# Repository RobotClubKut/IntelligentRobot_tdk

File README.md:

# Intelligent_robo_tdk
##知能ロボ2016多田機

###進捗メモ　　
カラーセンサーのバグを修正する  
ボール取って帰ってくる処理を綺麗にする  
先端のサーボを変更した   

なんかコーナーのビニテ直したらうまくいった  
フィールドマジ大切

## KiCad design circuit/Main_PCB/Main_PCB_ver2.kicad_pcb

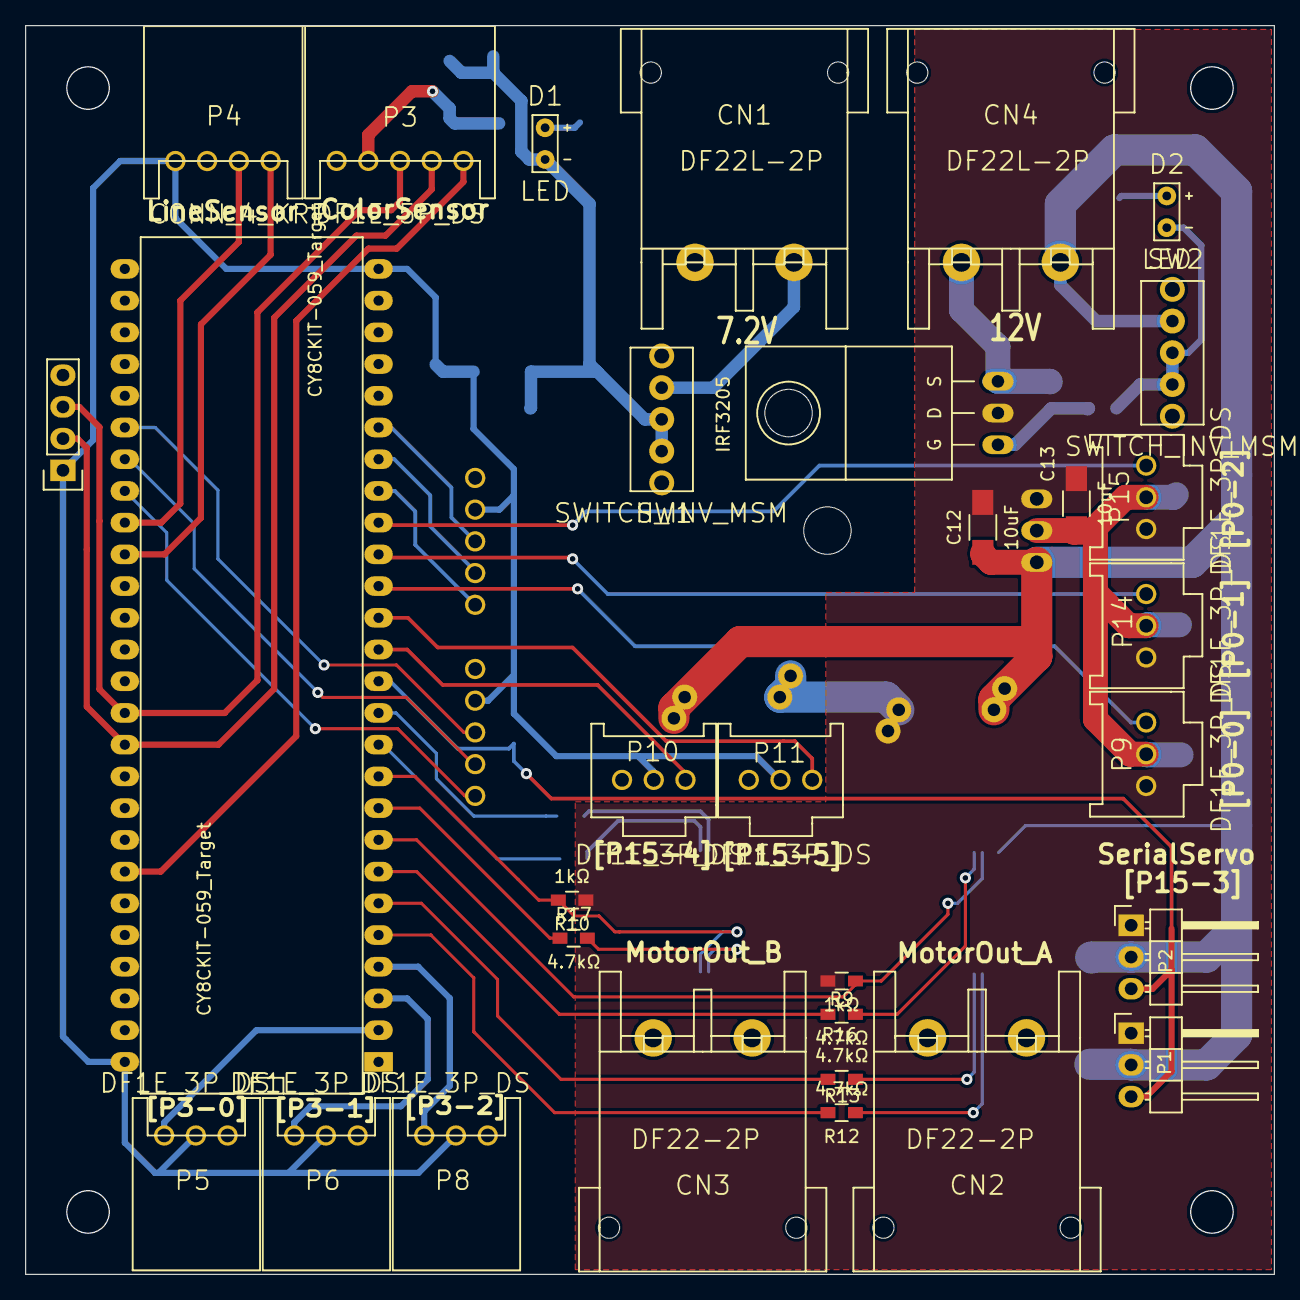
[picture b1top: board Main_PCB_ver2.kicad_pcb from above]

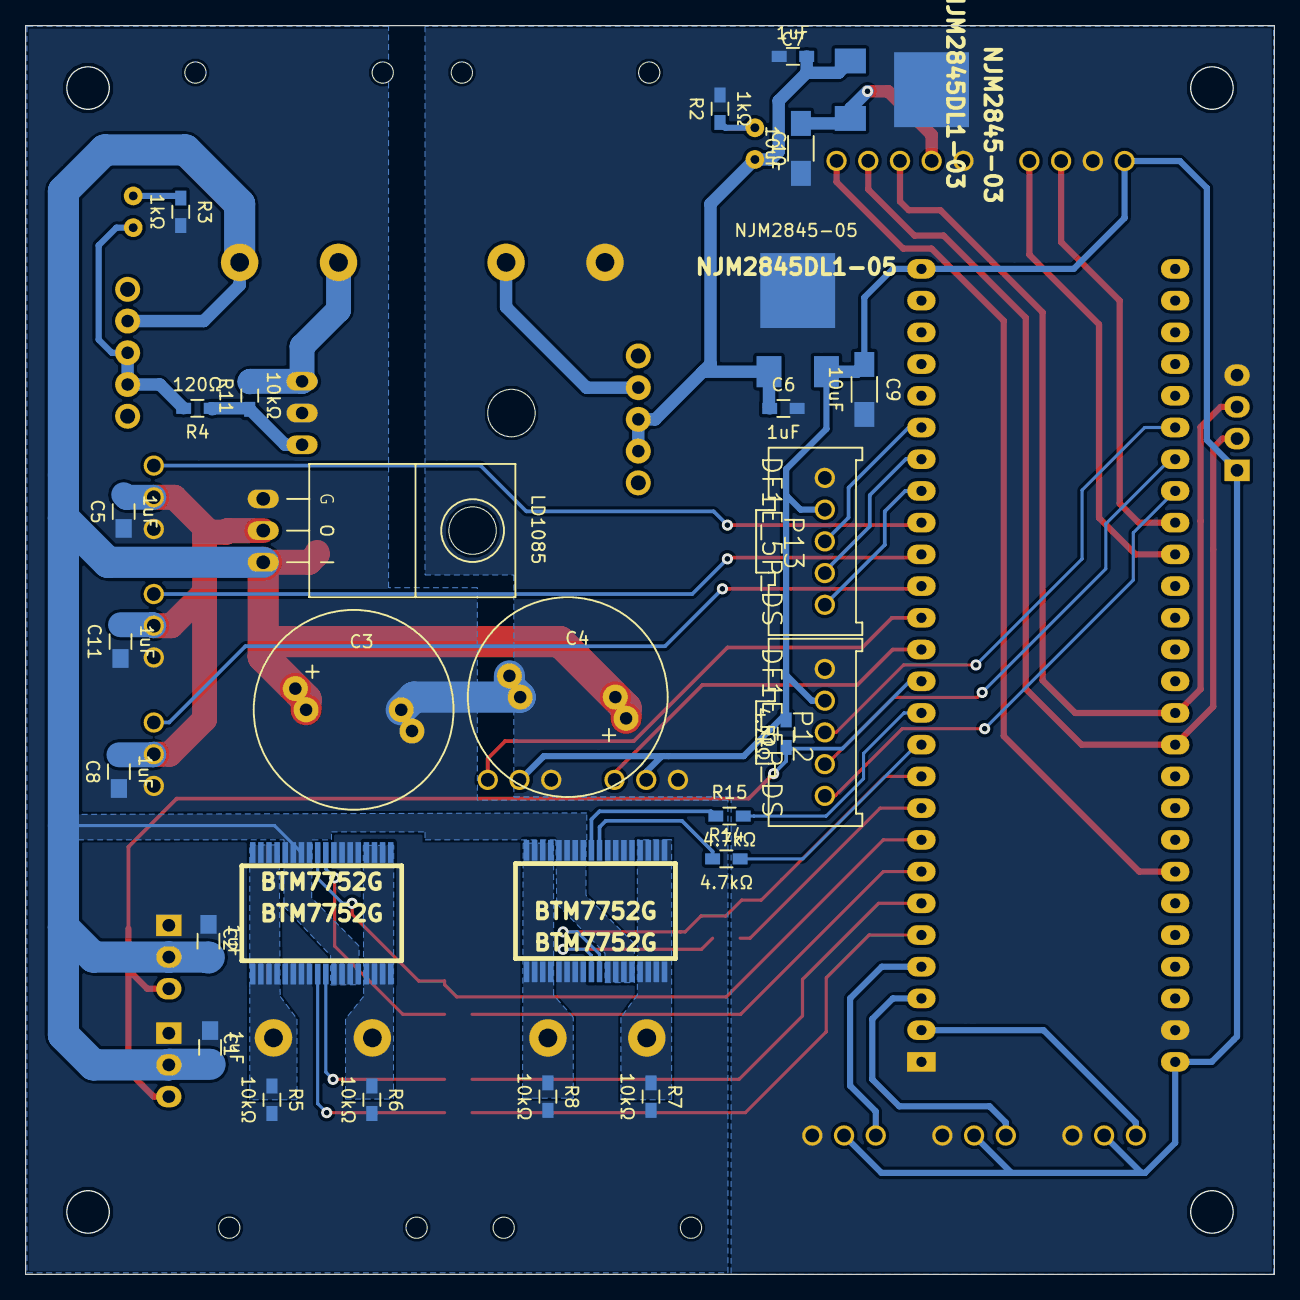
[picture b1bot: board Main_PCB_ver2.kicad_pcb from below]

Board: 2 copper layers, 100.0 x 100.0 mm, 60 parts (29 on the bottom side), 50 nets.

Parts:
BTM7752G, BTM7752G#2: BTM7752G; PG-DSO-36
C1, C2, C5, C8, C11: 1uF; R_0805_HandSoldering
C3, C4: 1000uF; Elko_vert_18x10mm_RM7.5to9_CopperClear
C6, C7: 1uF; R_0603_HandSoldering
C9, C10: 10uF; C_1206_HandSoldering
C12, C13: 10uF; R_1206_HandSoldering
CN1, CN4: DF22L-2P; CONN_RED_2P
CN2, CN3: DF22-2P; CONN_RED_2P
CY8CKIT-059_Target: CY8CKIT-059_Target; PSoC_5LP_Prototyping_Kit
D1, D2: LED; LED_HL_REG
IRF3205: MOS_N+pad; TO-220_FET-GDS_Horizontal
LD1085: NJM78M05FA; TO-220_LD1085
NJM2845-03: NJM2845DL1-03; TA48m33smd
NJM2845-05: NJM2845DL1-05; TA48m33smd
P1, P2: CONN_01X03; Pin_Header_Angled_1x03
P3: DF1E_5P_DS; DF1E_5P
P4: CONN_4_KRP; DF1E_4P
P5, P6, P8: DF1E_3P_DS; DF1E_3P
P7: CONN_01X04; Socket_Strip_Straight_1x04
P9, P10, P11, P14, P15: DF1E_3P_DS; DF1E_3P_S
P12, P13: DF1E_5P_DS; DF1E_5P_S
R1, R12, R13, R14, R15, R16, R17: 4.7kΩ; R_0603_HandSoldering
R2, R3, R9, R10: 1kΩ; R_0603_HandSoldering
R4: 120Ω; R_0603_HandSoldering
R5, R6, R7, R8, R11: 10kΩ; R_0603_HandSoldering
SW1, SW2: SWITCH_INV_MSM; Toggle_Switch_1L

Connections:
+3V3: C10.1, NJM2845-03.2, P3.2
+5V: C9.1, CY8CKIT-059_Target.26, CY8CKIT-059_Target.52, NJM2845-05.2, P4.1, P5.2, P6.2, P7.1, P8.2, P10.2, P11.2, P12.2, P13.2, R1.1
+8V: CN1.1, SW1.1
/motor/motor_a-OUT1: BTM7752G.15, BTM7752G.16, BTM7752G.17, BTM7752G.18, BTM7752G.19, BTM7752G.20, BTM7752G.21, BTM7752G.22, CN2.1, R6.1
/motor/motor_a-OUT2: BTM7752G.1, BTM7752G.2, BTM7752G.3, BTM7752G.4, BTM7752G.33, BTM7752G.34, BTM7752G.35, BTM7752G.36, CN2.2, R5.1
/motor/motor_b-OUT1: BTM7752G#2.15, BTM7752G#2.16, BTM7752G#2.17, BTM7752G#2.18, BTM7752G#2.19, BTM7752G#2.20, BTM7752G#2.21, BTM7752G#2.22, CN3.2, R8.1
/motor/motor_b-OUT2: BTM7752G#2.1, BTM7752G#2.2, BTM7752G#2.3, BTM7752G#2.4, BTM7752G#2.33, BTM7752G#2.34, BTM7752G#2.35, BTM7752G#2.36, CN3.1, R7.1
A_1: CY8CKIT-059_Target.21, P13.3
A_2: CY8CKIT-059_Target.32, P12.3
B_1: CY8CKIT-059_Target.20, P13.4
B_2: CY8CKIT-059_Target.33, P12.4
COLOR_SCL: CY8CKIT-059_Target.42, P3.4, P7.2
COLOR_SDA: CY8CKIT-059_Target.41, P3.3, P7.3
D_Sensor_1: CY8CKIT-059_Target.2, P5.3
D_Sensor_2: CY8CKIT-059_Target.3, P6.3
D_Sensor_3: CY8CKIT-059_Target.4, P8.3
GND: BTM7752G.5, BTM7752G.6, BTM7752G.7, BTM7752G.8, BTM7752G.23, BTM7752G.24, BTM7752G.25, BTM7752G.26, BTM7752G#2.5, BTM7752G#2.6, BTM7752G#2.7, BTM7752G#2.8, BTM7752G#2.23, BTM7752G#2.24, BTM7752G#2.25, BTM7752G#2.26, C1.2, C2.2, C3.2, C4.2, C5.1, C6.2, C7.2, C8.1, C9.2, C10.2, C11.1, C12.2, C13.2, CN1.2, CY8CKIT-059_Target.1, CY8CKIT-059_Target.51, IRF3205.D, LD1085.2, NJM2845-03.3, NJM2845-05.3, P1.1, P2.1, P3.1, P4.2, P5.1, P6.1, P7.4, P8.1, P9.1, P10.1, P11.1, P12.1, P13.1, P14.1, P15.1, R2.2, R3.2, R5.2, R6.2, R7.2, R8.2, R9.1, R10.1
INH_a: CY8CKIT-059_Target.7, R16.1
INH_b: CY8CKIT-059_Target.9, R17.1
IN_a-1: CY8CKIT-059_Target.5, R12.2
IN_a-2: CY8CKIT-059_Target.6, R13.2
IN_b-1: CY8CKIT-059_Target.11, R14.2
IN_b-2: CY8CKIT-059_Target.12, R15.2
IS_a: BTM7752G.28, CY8CKIT-059_Target.8, R9.2
IS_b: BTM7752G#2.28, CY8CKIT-059_Target.10, R10.2
unnamed: C6.1, C7.1, D1.2, NJM2845-03.1, NJM2845-05.1, SW1.2, SW1.3
unnamed: CN4.2, IRF3205.S, R11.2
unnamed: D1.1, R2.1
unnamed: D2.1, R3.1
unnamed: D2.2, R4.2, SW2.2, SW2.3
unnamed: BTM7752G.9, R12.1
unnamed: BTM7752G.10, R13.1
unnamed: BTM7752G#2.9, R14.1
unnamed: BTM7752G#2.10, R15.1
unnamed: BTM7752G.27, R16.2
unnamed: BTM7752G#2.27, R17.2
PowerSW: IRF3205.G, R4.1, R11.1
RX/LineSensor: CY8CKIT-059_Target.36, P4.4
Serial_Servo: CY8CKIT-059_Target.13, P1.3, P2.3, R1.2
Servo_PWM_1: CY8CKIT-059_Target.16, P9.3
Servo_PWM_2: CY8CKIT-059_Target.17, P14.3
Servo_PWM_3: CY8CKIT-059_Target.18, P15.3
Servo_PWR: C5.2, C8.2, C11.2, C13.1, LD1085.3, P9.2, P14.2, P15.2
TX/LineSensor: CY8CKIT-059_Target.35, P4.3
VS: BTM7752G.11, BTM7752G.12, BTM7752G.13, BTM7752G.14, BTM7752G.29, BTM7752G.30, BTM7752G.31, BTM7752G.32, BTM7752G#2.11, BTM7752G#2.12, BTM7752G#2.13, BTM7752G#2.14, BTM7752G#2.29, BTM7752G#2.30, BTM7752G#2.31, BTM7752G#2.32, C1.1, C2.1, C3.1, C4.1, C12.1, CN4.1, LD1085.1, P1.2, P2.2, SW2.1
Z_1: CY8CKIT-059_Target.19, P13.5
Z_2: CY8CKIT-059_Target.34, P12.5
sensor_LED: CY8CKIT-059_Target.46, P3.5
some_pin_1: CY8CKIT-059_Target.14, P10.3
some_pin_2: CY8CKIT-059_Target.15, P11.3

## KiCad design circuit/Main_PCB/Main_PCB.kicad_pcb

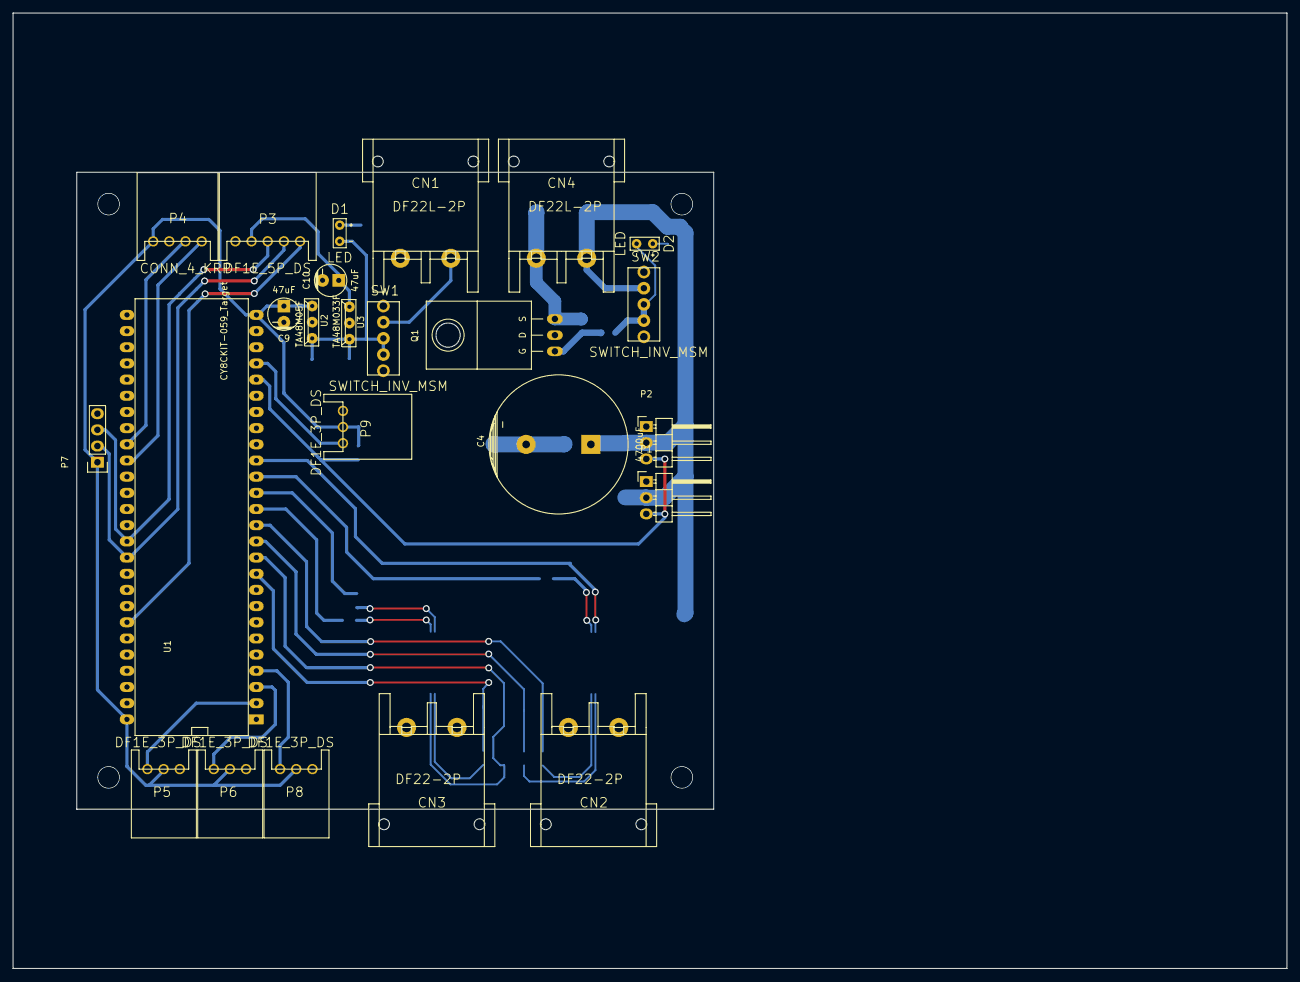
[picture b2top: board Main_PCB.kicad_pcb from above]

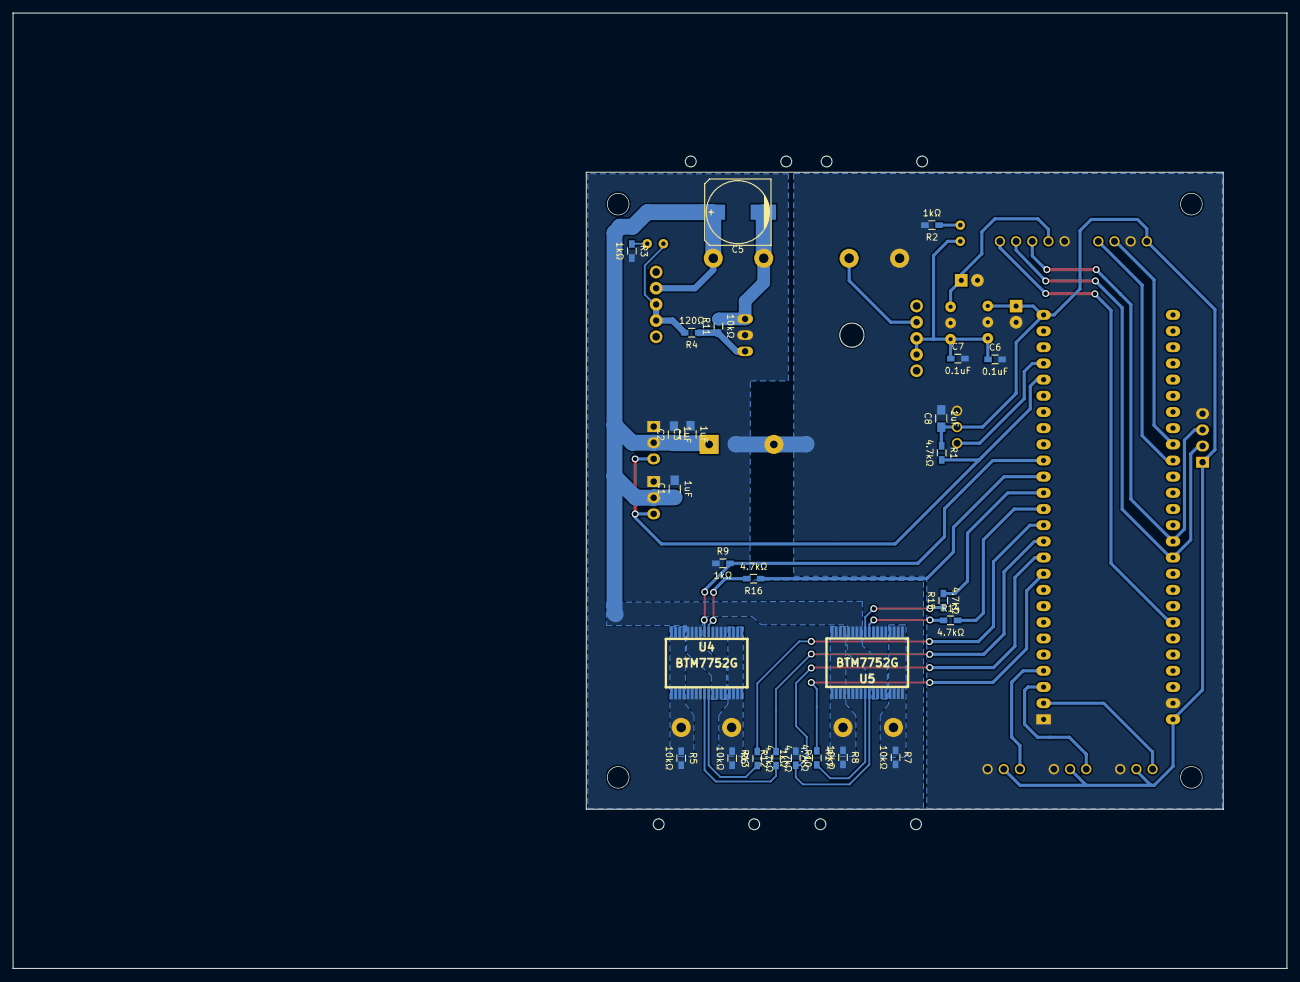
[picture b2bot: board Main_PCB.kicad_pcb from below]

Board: 2 copper layers, 200.0 x 150.0 mm, 50 parts (26 on the bottom side), 39 nets.

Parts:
C1, C2, C3, C8: 1uF; R_0805_HandSoldering
C4: 4700uF; Capacitor22x41RM10
C5: 330uF; c_elec_10x7.7
C6, C7: 0.1uF; R_0603_HandSoldering
C9, C10: 47uF; Capacitor5x6RM2.5
CN1, CN4: DF22L-2P; CONN_RED_2P
CN2, CN3: DF22-2P; CONN_RED_2P
D1, D2: LED; LED_HL_REG
P1, P2: CONN_01X03; Pin_Header_Angled_1x03
P3: DF1E_5P_DS; DF1E_5P
P4: CONN_4_KRP; DF1E_4P
P5, P6, P8, P9: DF1E_3P_DS; DF1E_3P
P7: CONN_01X04; Socket_Strip_Straight_1x04
Q1: MOS_N+pad; TO-220_FET-GDS_Horizontal
R1, R12, R13, R14, R15, R16, R17: 4.7kΩ; R_0603_HandSoldering
R2, R3, R9, R10: 1kΩ; R_0603_HandSoldering
R4: 120Ω; R_0603_HandSoldering
R5, R6, R7, R8, R11: 10kΩ; R_0603_HandSoldering
SW1, SW2: SWITCH_INV_MSM; Toggle_Switch_1L
U1: CY8CKIT-059_Target; PSoC_5LP_Prototyping_Kit
U2: TA48M05F
U3: TA48M033F; TA48M05F
U4, U5: BTM7752G; PG-DSO-36

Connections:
+3V3: C10.1, P3.2, U3.2
+5V: C8.1, C9.1, P4.1, P5.2, P6.2, P7.1, P8.2, P9.2, R1.1, U1.26, U1.52, U2.2
+8V: CN1.1, SW1.1
/motor/motor_a-OUT1: CN2.1, R6.1, U4.15, U4.16, U4.17, U4.18, U4.19, U4.20, U4.21, U4.22
/motor/motor_a-OUT2: CN2.2, R5.1, U4.1, U4.2, U4.3, U4.4, U4.33, U4.34, U4.35, U4.36
/motor/motor_b-OUT1: CN3.2, R8.1, U5.15, U5.16, U5.17, U5.18, U5.19, U5.20, U5.21, U5.22
/motor/motor_b-OUT2: CN3.1, R7.1, U5.1, U5.2, U5.3, U5.4, U5.33, U5.34, U5.35, U5.36
COLOR_SCL: P3.4, P7.2, U1.42
COLOR_SDA: P3.3, P7.3, U1.41
GND: C1.2, C2.2, C3.2, C4.2, C6.2, C7.2, C8.2, C9.2, C10.2, CN1.2, P1.1, P2.1, P3.1, P4.2, P5.1, P6.1, P7.4, P8.1, P9.1, Q1.D, R2.2, R3.2, R5.2, R6.2, R7.2, R8.2, R9.1, R10.1, U1.1, U1.51, U2.3, U3.3, U4.5, U4.6, U4.7, U4.8, U4.23, U4.24, U4.25, U4.26, U5.5, U5.6, U5.7, U5.8, U5.23, U5.24, U5.25, U5.26
INH_a: R16.1, U1.16
INH_b: R17.1, U1.10
IN_a-1: R12.2, U1.12
IN_a-2: R13.2, U1.13
IN_b-1: R14.2, U1.14
IN_b-2: R15.2, U1.15
IS_a: R9.2, U1.17, U4.28
IS_b: R10.2, U1.11, U5.28
unnamed: C5.2, CN4.2, Q1.S, R11.2
unnamed: C6.1, C7.1, D1.2, SW1.2, SW1.3, U2.1, U3.1
unnamed: D1.1, R2.1
unnamed: D2.1, R3.1
unnamed: D2.2, R4.2, SW2.2, SW2.3
unnamed: R12.1, U4.9
unnamed: R13.1, U4.10
unnamed: R14.1, U5.9
unnamed: R15.1, U5.10
unnamed: R16.2, U4.27
unnamed: R17.2, U5.27
PIN_1: P5.3, U1.2
PIN_2: P6.3, U1.3
PIN_3: P8.3, U1.4
PIN_PWM: P9.3, U1.23
PowerSW: Q1.G, R4.1, R11.1
RX/LineSensor: P4.4, U1.36
Servo: P1.3, P2.3, R1.2, U1.22
TX/LineSensor: P4.3, U1.35
VS: C1.1, C2.1, C3.1, C4.1, C5.1, CN4.1, P1.2, P2.2, SW2.1, U4.11, U4.12, U4.13, U4.14, U4.29, U4.30, U4.31, U4.32, U5.11, U5.12, U5.13, U5.14, U5.29, U5.30, U5.31, U5.32
sensor_LED: P3.5, U1.46

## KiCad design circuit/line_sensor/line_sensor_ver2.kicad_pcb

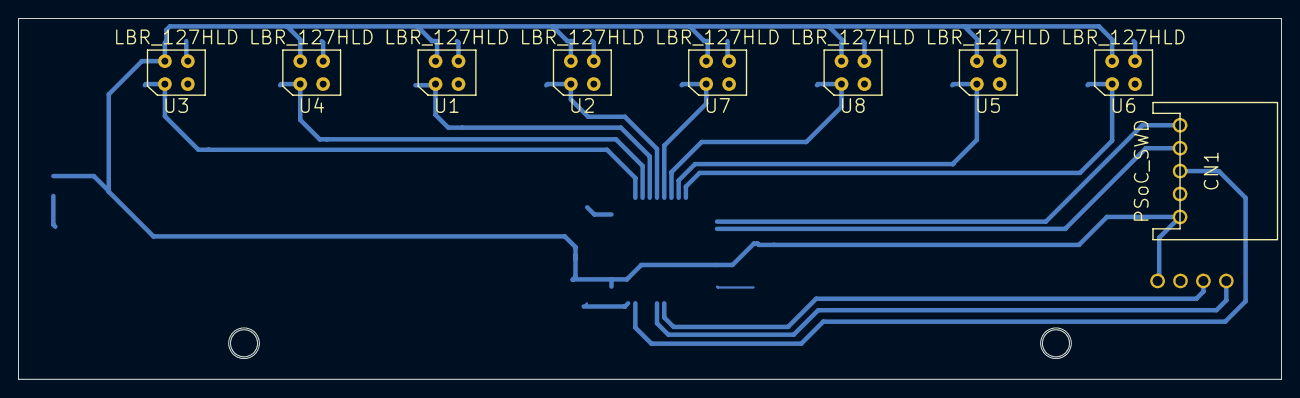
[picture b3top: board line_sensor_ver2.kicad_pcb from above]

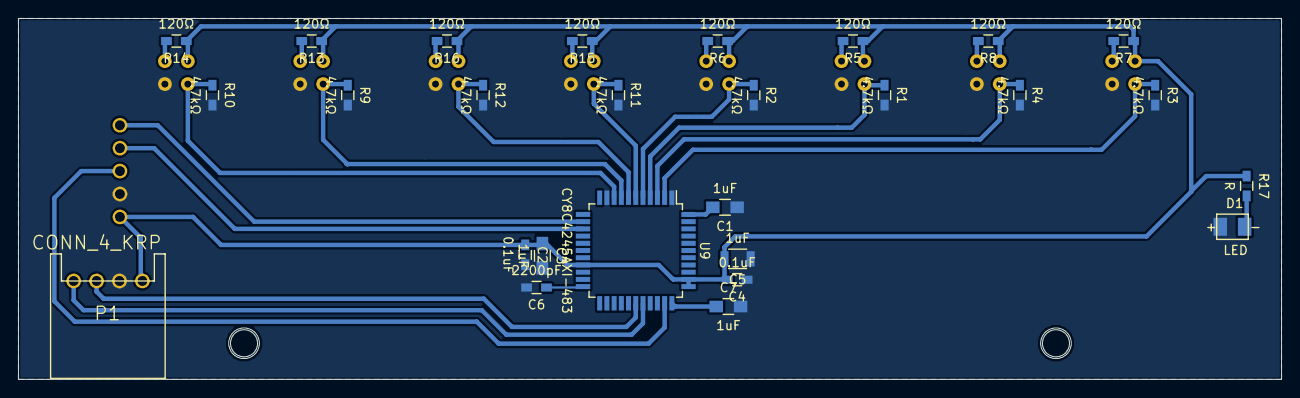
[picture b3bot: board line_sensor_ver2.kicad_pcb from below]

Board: 2 copper layers, 140.0 x 40.0 mm, 36 parts (27 on the bottom side), 26 nets.

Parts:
C1, C3, C7: 1uF; R_0805_HandSoldering
C2, C4: 0.1uF; R_0603_HandSoldering
C5: 1uF; R_1206
C6: 2200pF; R_0603_HandSoldering
CN1: PSoC_SWD; DF1E_5P
D1: LED; LED_3528
P1: CONN_4_KRP; DF1E_4P
R1, R2, R3, R4, R9, R10, R11, R12: 4.7kΩ; R_0603_HandSoldering
R5, R6, R7, R8, R13, R14, R15, R16: 120Ω; R_0603_HandSoldering
R17: R; R_0603_HandSoldering
U1, U2, U3, U4, U5, U6, U7, U8: LBR_127HLD; RPR-220
U9: CY8C4245AXI-483; LQFP-44_10x10mm_Pitch0.8mm

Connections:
+5V: C2.1, C3.1, C4.2, C5.2, C7.1, CN1.5, P1.1, R5.1, R6.1, R7.1, R8.1, R13.1, R14.1, R15.1, R16.1, R17.1, U1.4, U2.4, U3.4, U4.4, U5.4, U6.4, U7.4, U8.4, U9.19, U9.33, U9.34, U9.35
GND: C1.1, C2.2, C3.2, C4.1, C5.1, C6.2, C7.2, CN1.4, D1.1, P1.2, R1.2, R2.2, R3.2, R4.2, R9.2, R10.2, R11.2, R12.2, U1.2, U2.2, U3.2, U4.2, U5.2, U6.2, U7.2, U8.2, U9.1, U9.10
unnamed: C1.2, U9.44
unnamed: C6.1, U9.22
unnamed: D1.2, R17.2
unnamed: R5.2, U1.1
unnamed: R6.2, U2.1
unnamed: R7.2, U3.1
unnamed: R8.2, U4.1
unnamed: R13.2, U5.1
unnamed: R14.2, U6.1
unnamed: R15.2, U7.1
unnamed: R16.2, U8.1
PIN_1: R3.1, U3.3, U9.2
PIN_2: R4.1, U4.3, U9.3
PIN_3: R1.1, U1.3, U9.4
PIN_4: R2.1, U2.3, U9.5
PIN_5: R11.1, U7.3, U9.6
PIN_6: R12.1, U8.3, U9.7
PIN_7: R9.1, U5.3, U9.8
PIN_8: R10.1, U6.3, U9.9
SWDCLK: CN1.2, U9.14
SWDIO: CN1.1, U9.13
UART/RX: P1.3, U9.28
UART/TX: P1.4, U9.29
XRES: CN1.3, U9.32

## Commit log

2016-04-20 プロジェクトの追加
2016-04-21 PWMのServo動かした
2016-04-22 スイッチの追加
2016-04-22 サーボで掴む処理を追加
2016-04-26 サーボのプログラム書いた
2016-04-27 覚え書き
2016-04-28 タイマーの追加
2016-04-28 サーボの動きだいたいできた
2016-04-28 雛形作り始め
2016-04-28 カラーセンサーの処理追加
2016-04-28 次の課題を追加
2016-05-18 距離センサーの処理の追加
2016-05-18 ラインセンサに変化判定を追加
2016-05-18 構造体作った
2016-05-20 ヘッダー分けた
2016-05-20 テニスボール捨てるところまでできた
2016-05-20 ボール探査エリアまで行けた
2016-05-21 ライントレースを改良
2016-05-21 デバッグの追加
2016-05-21 デバッグモードの追加
2016-05-22 旋回する動きまで出来た
2016-05-23 関数の追加
2016-05-24 探査はできた
2016-05-25 ライントレースよくなった
2016-05-25 サーチモードできた
2016-05-25 エンコーダーの処理を追加
2016-05-27 PIDで走るように変更
2016-05-29 フルカラーLEDのモジュール追加
2016-05-29 ボール取りに行くところまでできた
2016-06-06 フルカラーLED使えそう
2016-06-06 アプローチ関数つくり込む
2016-06-07 アプローチ関数ほぼできた
2016-06-07 アプローチ関数改良
2016-06-07 ボール取って帰ってこれた
2016-06-08 ボールシュートするとこ作りかけ
2016-06-08 サーボをシリアルのものに変更
2016-06-10 モーターを16bitに変更
2016-06-10 モーターのPID制御できた
2016-06-10 ライントレース今度こそできた
2016-06-11 モーター回りは今度こそ完成
2016-06-11 ボールをシュートするとこ書いた
2016-06-12 カラーセンサーの処理完成
2016-06-13 アプローチ関数がんばる
2016-06-14 PID使わない予定
2016-06-15 スイッチ追加
2016-06-15 ラインセンサの処理を高速化
2016-06-15 スタートの関数追加
2016-06-16 フルカラーLEDの処理を追加
2016-06-16 ほぼ完成
2016-06-18 フルカラーLEDは光ってるだけ
2019-10-07 add kicad project
